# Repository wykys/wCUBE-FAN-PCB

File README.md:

# wCUBE-FAN-PCB
Expand board for RAMPS 1.4

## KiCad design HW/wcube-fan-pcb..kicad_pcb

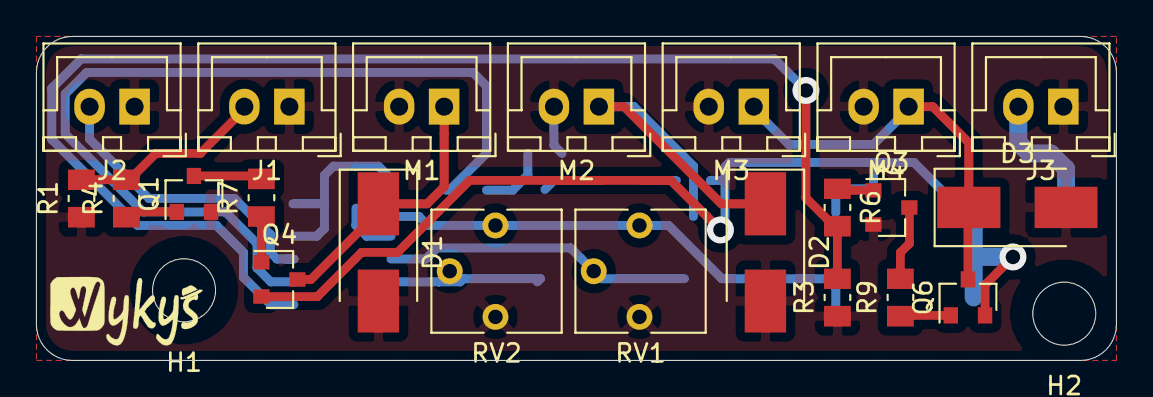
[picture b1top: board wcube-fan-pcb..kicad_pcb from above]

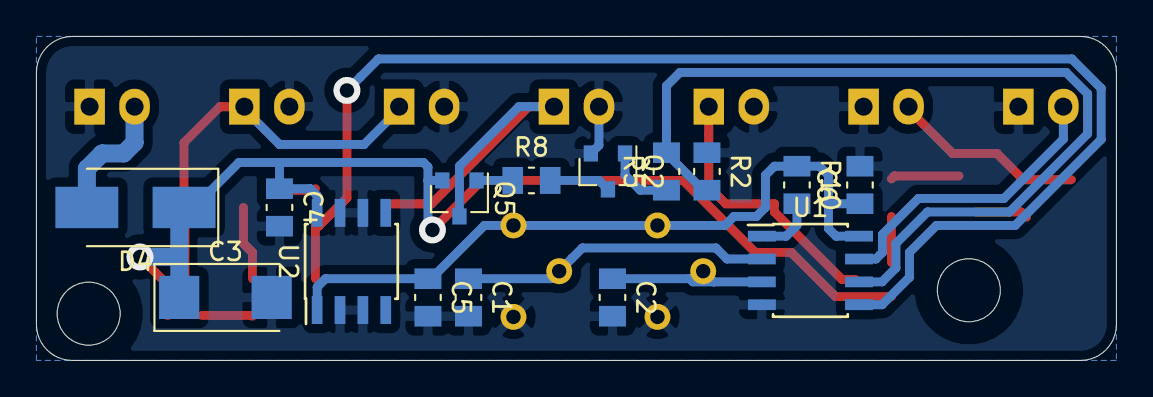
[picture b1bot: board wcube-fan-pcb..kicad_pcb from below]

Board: 2 copper layers, 60.0 x 18.0 mm, 40 parts (15 on the bottom side), 23 nets.

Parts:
C1, C2, C4, C5, C6: 100n; C_0805_2012Metric_Pad1.15x1.50mm_HandSolder
C3: 22u/16V; CP_EIA-6032-28_Kemet-C_Pad2.24x2.40mm_HandSolder
D1, D2, D3, D4: SS24; D_SMB_Handsoldering
GR1: Wykys; wykys_small_skill
H1, H2: M3; Bolt_M3
J1: HOT_END; JST_XH_B02B-XH-A_1x02_P2.50mm_Vertical
J2: ON_~OFF; JST_XH_B02B-XH-A_1x02_P2.50mm_Vertical
J3: POWER; JST_XH_B02B-XH-A_1x02_P2.50mm_Vertical
M1, M2, M3, M4: Fan; JST_XH_B02B-XH-A_1x02_P2.50mm_Vertical
Q1, Q2, Q3: BC817; SOT-23
Q4, Q5, Q6: BC807; SOT-23
R1, R2, R3, R4, R5, R6, R10: 100k; R_0805_2012Metric_Pad1.15x1.50mm_HandSolder
R7, R8, R9: 2k2; R_0805_2012Metric_Pad1.15x1.50mm_HandSolder
RV1, RV2: 10k; Potentiometer_Vishay_T73YP_Vertical
U1: ATTINY13A-SSU; SOIC-8_3.9x4.9mm_P1.27mm
U2: L78L05_SO8; SOIC-8_3.9x4.9mm_P1.27mm

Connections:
+5V: C5.1, C6.1, R10.1, RV1.1, RV2.1, U1.8, U2.1
+12V: C3.1, C4.1, D4.1, Q4.2, Q5.2, Q6.2, U2.8
/ADC_BOX: C1.1, RV1.2, U1.2
/ADC_HEAD: C2.1, RV2.2, U1.3
/ON_~OFF: J2.2, U1.7
/PWM_BOX: R3.2, R6.2, U1.5
/PWM_HEAD: R2.2, R5.2, U1.6
/PWM_HOT_END: J1.2, R1.2, R4.2
GND: C1.2, C2.2, C3.2, C4.2, C5.2, C6.2, D1.2, D2.2, D3.2, J1.1, J2.1, J3.1, M1.2, M2.2, M3.2, M4.2, Q1.2, Q2.2, Q3.2, R1.1, R2.1, R3.1, RV1.3, RV2.3, U1.4, U2.2, U2.3, U2.6, U2.7
unnamed: D1.1, M1.1, Q4.3
unnamed: D2.1, M2.1, Q5.3
unnamed: D3.1, M3.1, M4.1, Q6.3
unnamed: D4.2, J3.2
unnamed: Q1.1, R4.1
unnamed: Q1.3, R7.2
unnamed: Q2.1, R5.1
unnamed: Q2.3, R8.2
unnamed: Q3.1, R6.1
unnamed: Q3.3, R9.2
unnamed: Q4.1, R7.1
unnamed: Q5.1, R8.1
unnamed: Q6.1, R9.1
unnamed: R10.2, U1.1

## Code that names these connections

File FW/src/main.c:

/*
    wykys 2019
    PWM fan regulator for expand RAMPS 1.4 wCUBE board
*/

#include "settings.h"
#include <avr/io.h>
#include <avr/interrupt.h>

#define PIN_PWM_BOX PB0
#define PIN_PWM_HEAD PB1
#define PIN_ADC_BOX PB4
#define PIN_ADC_HEAD PB3
#define PIN_ONOFF PB2

#define OCR_BOX OCR0A
#define OCR_HEAD OCR0B

#define ADC_CHANNEL_BOX 3
#define ADC_CHANNEL_HEAD 2
#define ADC_CHANNEL_DEFAULT ADC_CHANNEL_HEAD
#define ADC_SAMPLES_LEN 13

FUSES = {
    .low = 0x3A,
    .high = 0xFF,
};

void gpio_init(void)
{
    DDRB = (1 << PIN_PWM_BOX) | (1 << PIN_PWM_HEAD);
    PORTB = (1 << PIN_ONOFF);
}

void timer_init(void)
{
    TCCR0A = (1 << COM0A1) | (1 << COM0B1) | // clear OC0x on compare match, set OC0x at TOP
             (1 << WGM01) | (1 << WGM00);    // mode 3 fast PWM
    TCCR0B = (1 << CS00);                    // clk = F_CPU
    TIMSK0 = (1 << TOIE0);                   // enable overflow interrupt
    TCNT0 = 0;                               // clear timer
    OCR_BOX = 1;
    OCR_HEAD = 0xFF;
}

void adc_init(void)
{
    ADMUX = (1 << ADLAR);               // left align from h byte bits 9-2 in ADCH
    ADMUX |= ADC_CHANNEL_DEFAULT;       // set default channel
    ADCSRA = (1 << ADEN) | (1 << ADIE); // enable ADC, adc_clk = F_CPU/2, enable interrupt
    ADCSRB = (1 << ADTS2);              // trigger on timer overflow
    ADCSRA |= (1 << ADATE);             // start conversion with trigger
}

ISR(TIM0_OVF_vect)
{
    // this interrupt is trigger for ADC
}

ISR(ADC_vect)
{
    uint16_t average;
    uint8_t channel = ADMUX & ((1 << MUX1) | (1 << MUX0));
    static uint8_t sample[ADC_SAMPLES_LEN] = {0};
    static uint8_t i = 0;

    sample[i++] = ADCH;

    if (i == ADC_SAMPLES_LEN)
    {
        ADCSRA &= ~(1 << ADEN);

        for (average = 0, i = 0; i < ADC_SAMPLES_LEN; i++)
            average += sample[i] * 10;
        average /= ADC_SAMPLES_LEN * 10;
        average = (bit_is_set(PINB, PIN_ONOFF)) ? average : 0;

        if (channel == ADC_CHANNEL_HEAD)
        {
            OCR_HEAD = average;
            channel = ADC_CHANNEL_BOX;
        }
        else
        {
            OCR_BOX = average;
            channel = ADC_CHANNEL_HEAD;
        }

        ADMUX &= ~((1 << MUX1) | (1 << MUX0));
        ADMUX |= channel;
        ADCSRA |= (1 << ADEN);

        i = 0;
    }
}

int main(void)
{
    gpio_init();
    adc_init();
    timer_init();
    sei();

    while (1)
        ;

    return 0;
}

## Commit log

2019-02-28 Created schematic
2019-03-01 Created layout
2019-03-01 Updated layout
2019-03-01 Updated edge cuts
2019-03-01 Added GERBER
2019-03-10 Added firmware
2019-03-16 Swapped ADC pins
